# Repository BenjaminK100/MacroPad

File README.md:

this is my custom key macropad using a seeed xiao rp2040. i built it mostly because i wanted something actually to help with Spotiy and shortcuts

it’s got a rotary encoder for volume, a small oled screen, and a 3x4 matrix its daily stuff like oping apps shuffle music ect.
right its

open firefox, spotify, discord
control volume with the knob
mute/unmute my mic
toggle vpn
run a timer that shows how long i’ve been working
show status on the screen (mic, vpn, timer)
still depding on wat annimation to use 

firmware is just circuitpython since it’s easy to change stuff quickly. might switch to qmk later but this works fine for now.

future stuff i might add:

better screen ui (icons instead of text)
animations
different modes depending on what i’m doing
proper linux integration instead of basic shortcuts

BOM
Seeed XIAO RP2040
1N4148 Diodes, 12, MX-Style switches, 12  MX-Style switches,0.91 inch OLED display, keycaps, 4x M3x16mm 
4x M3x5mx4mm heatset inserts

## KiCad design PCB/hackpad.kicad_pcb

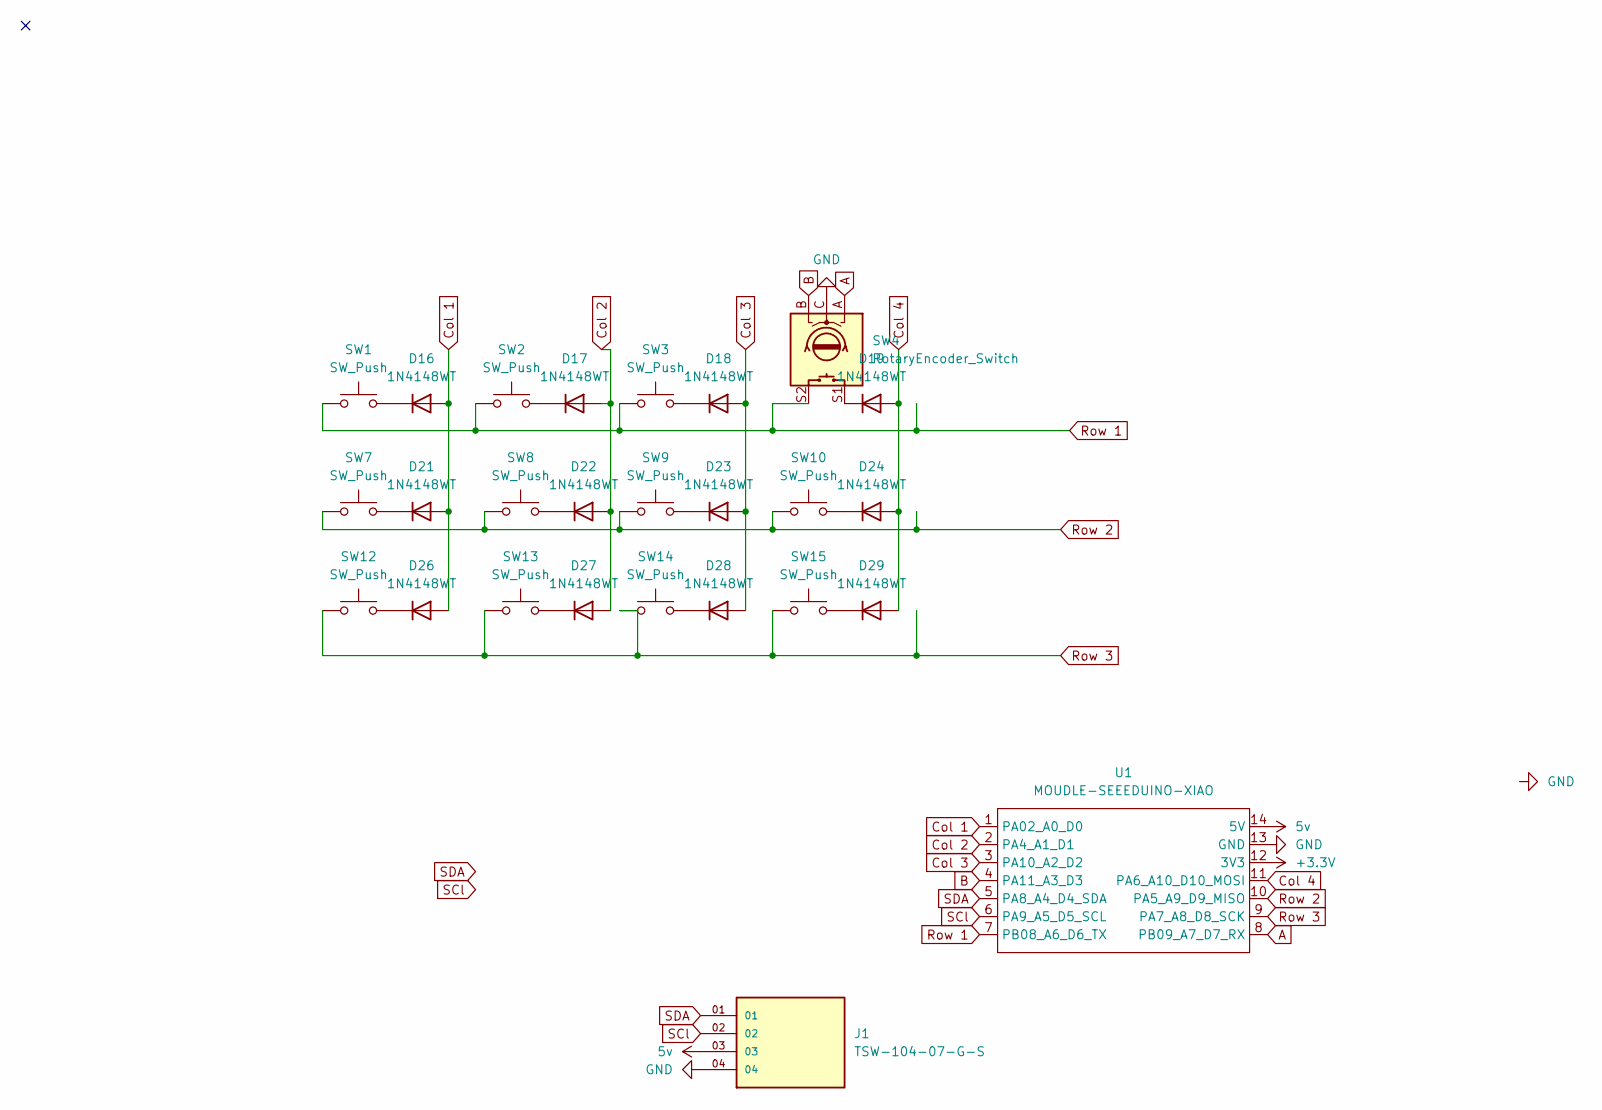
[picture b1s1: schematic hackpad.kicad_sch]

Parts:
D16, D17, D18, D19, D21, D22, D23, D24, D26, D27, D28, D29: 1N4148WT; DIOAD753W49L380D172B
J1: TSW-104-07-G-S; SAMTEC_TSW-104-07-G-S; PARTREV R
SW1, SW2, SW3, SW7, SW8, SW9, SW10, SW12, SW13, SW14, SW15: SW_Push; SW_Cherry_MX_1.00u_PCB
SW4: RotaryEncoder_Switch; RotaryEncoder_Alps_EC11E-Switch_Vertical_H20mm
U1: MOUDLE-SEEEDUINO-XIAO; MODULE_102010428

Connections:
5v: J1.03, U1.14 (5V)
+3.3V: U1.12 (3V3)
A: SW4.A, U1.8 (PB09_A7_D7_RX)
B: SW4.B, U1.4 (PA11_A3_D3)
Col 1: D16.2 (A), D21.2 (A), D26.2 (A), U1.1 (PA02_A0_D0)
Col 2: D17.2 (A), D22.2 (A), D27.2 (A), U1.2 (PA4_A1_D1)
Col 3: D18.2 (A), D23.2 (A), D28.2 (A), U1.3 (PA10_A2_D2)
Col 4: D19.2 (A), D24.2 (A), D29.2 (A), U1.11 (PA6_A10_D10_MOSI)
GND: J1.04, SW4.C, U1.13 (GND)
unnamed: D16.1 (K), SW1.2
unnamed: D17.1 (K), SW2.2
unnamed: D18.1 (K), SW3.2
unnamed: D19.1 (K), SW4.S1
unnamed: D21.1 (K), SW7.2
unnamed: D22.1 (K), SW8.2
unnamed: D23.1 (K), SW9.2
unnamed: D24.1 (K), SW10.2
unnamed: D26.1 (K), SW12.2
unnamed: D27.1 (K), SW13.2
unnamed: D28.1 (K), SW14.2
unnamed: D29.1 (K), SW15.2
Row 1: SW1.1, SW2.1, SW3.1, SW4.S2, U1.7 (PB08_A6_D6_TX)
Row 2: SW7.1, SW8.1, SW9.1, SW10.1, U1.10 (PA5_A9_D9_MISO)
Row 3: SW12.1, SW13.1, SW14.1, SW15.1, U1.9 (PA7_A8_D8_SCK)
SCl: J1.02, U1.6 (PA9_A5_D5_SCL)
SDA: J1.01, U1.5 (PA8_A4_D4_SDA)

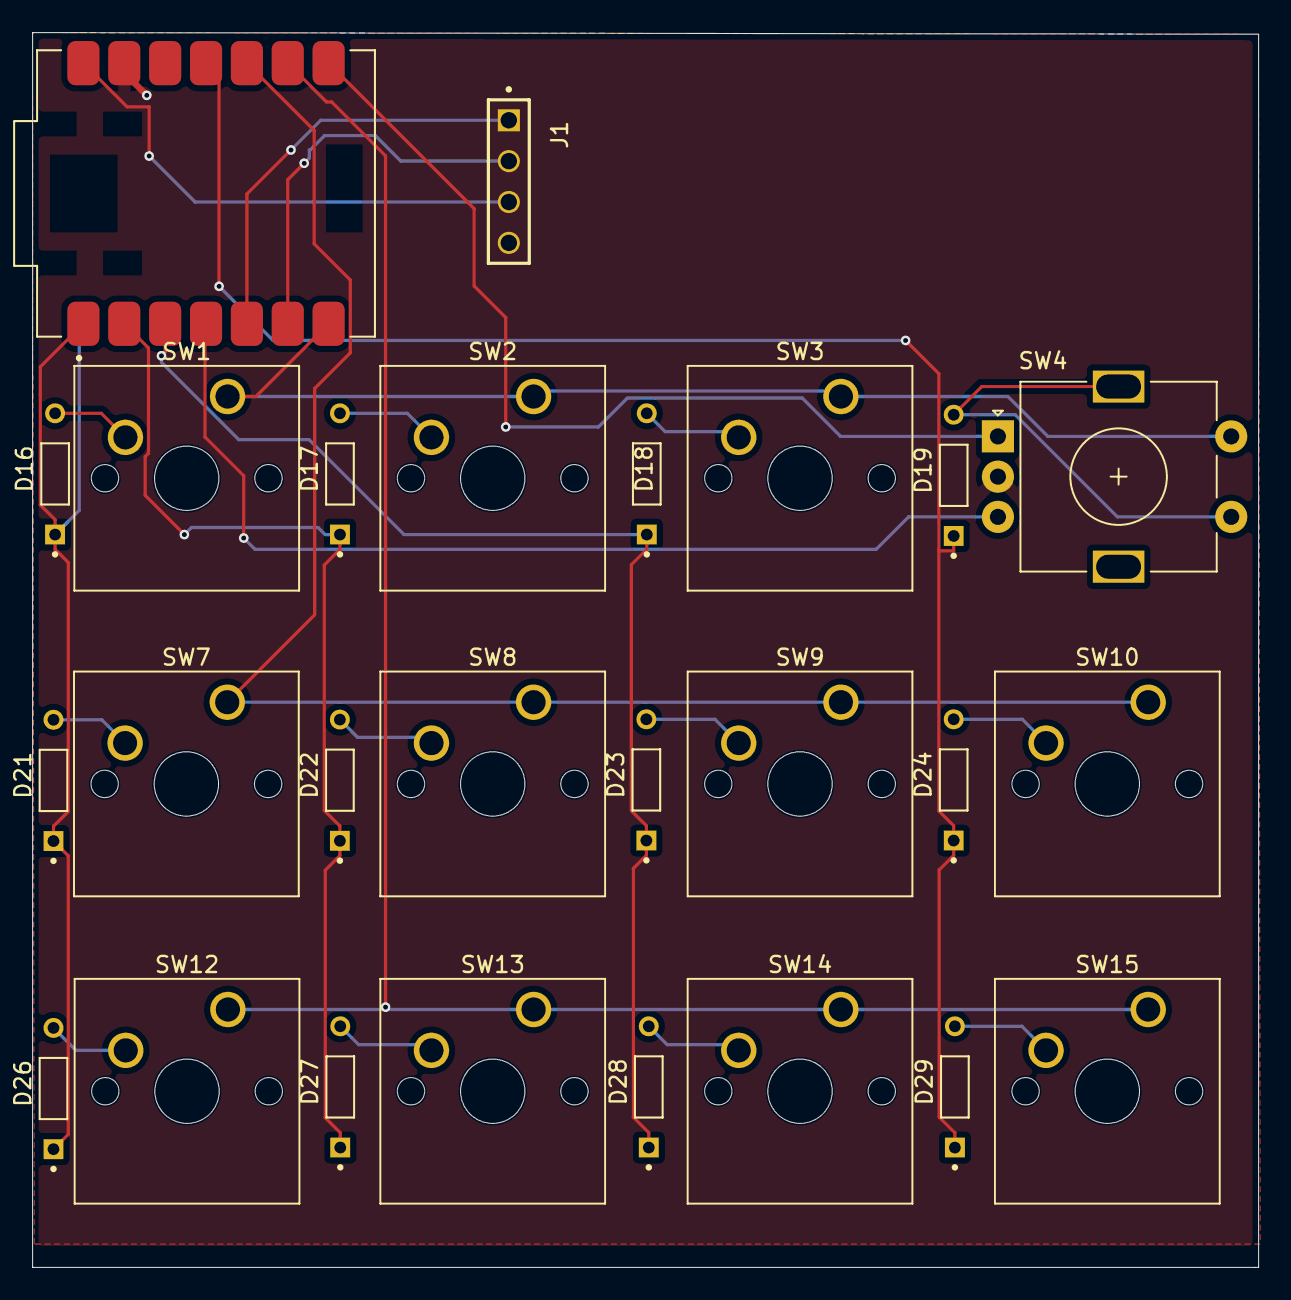
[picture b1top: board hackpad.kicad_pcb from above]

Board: 2 copper layers, 76.2 x 76.8 mm, 26 parts (0 on the bottom side), 25 nets.

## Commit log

2026-03-29 adding cad files
2026-04-01 added code
2026-04-01 added gerber fikes and pcb
2026-04-01 it should be a zip file oops
2026-04-01 added a real read me
2026-04-01 added images to read me
2026-04-01 will it wokr bnow
2026-04-01 gimage work now?
2026-04-01 wokr now?
    wokr
2026-04-01 moved it areorund
2026-04-01 added BOM
2026-04-01 added more imahe
2026-04-01 image
2026-04-01 inage work again
2026-04-01 chaned the read me
2026-04-01 chaed file main to gerbal
